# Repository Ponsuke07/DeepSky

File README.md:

View this project on [CADLAB.io](https://cadlab.io/project/1893). 

# DeepSky
*DeepSky* is a Open Source JTAG Adapter based on FTDI FT2232.  
*Deepsky* is also designed JTAGKey clone.

# Supported Software
[OpenOCD][1] support ([config file](./conf/openocd/deepsky.cfg)).  

[1]:http://openocd.org/

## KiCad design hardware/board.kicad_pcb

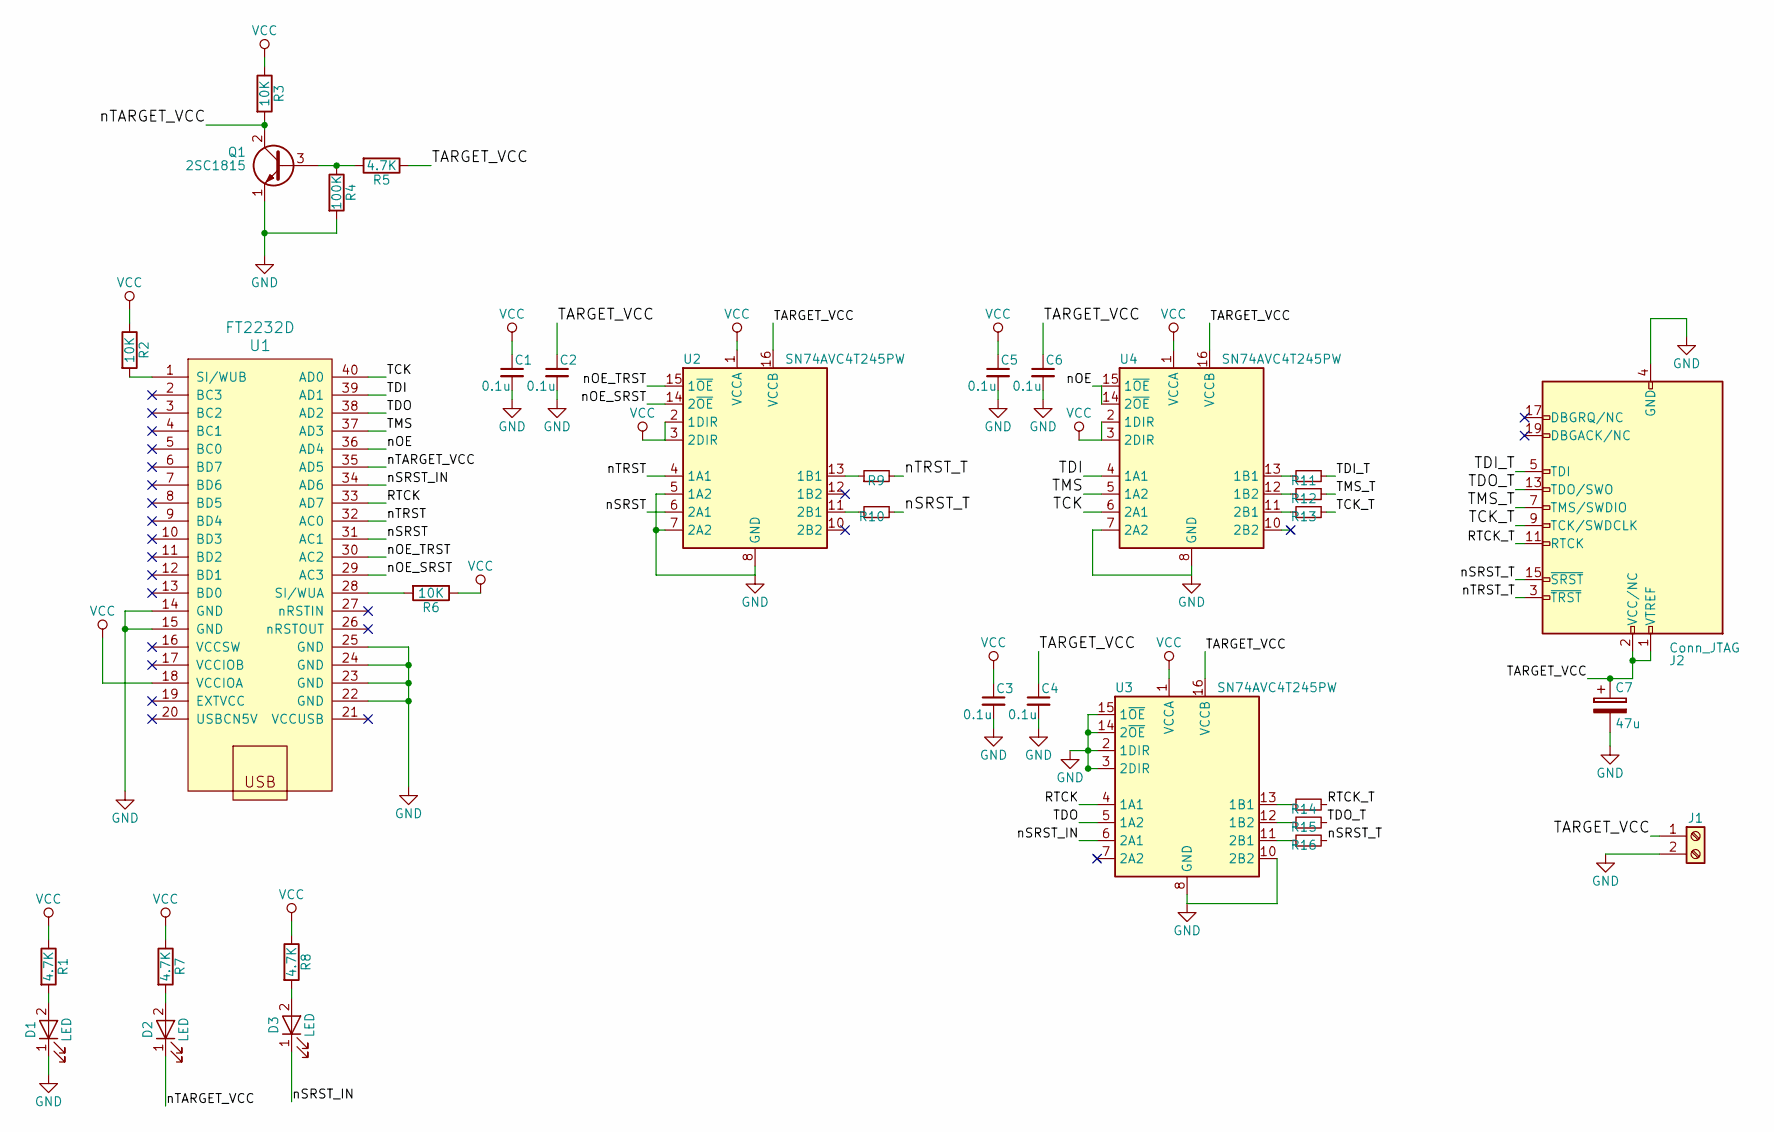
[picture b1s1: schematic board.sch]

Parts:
C1, C2, C3, C4, C5, C6: 0.1u; C_0805_HandSoldering
C7: 47u; CP_Elec_8x6.7
D1, D2, D3: LED; LED_D3.0mm
J1: Screw_Terminal_01x02; TerminalBlock_Phoenix_MKDS1.5-2pol
J2: Conn_JTAG; Pin_Header_Straight_2x10_Pitch2.54mm
Q1: 2SC1815; TO-92_Inline_Wide
R1, R5, R7, R8: 4.7K; R_0805_HandSoldering
R2, R3, R6: 10K; R_0805_HandSoldering
R4: 100K; R_Axial_DIN0207_L6.3mm_D2.5mm_P10.16mm_Horizontal
R9, R10, R11, R12, R13, R14, R15, R16: 68; R_0805_HandSoldering
U1: FT2232D; AE-FT2232
U2, U3, U4: SN74AVC4T245PW; TSSOP-16_4.4x5mm_P0.65mm

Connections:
/RTCK: U1.33 (AD7), U3.4 (1A1)
/RTCK_T: J2.11 (RTCK), R14.2
/TARGET_VCC: C2.1, C4.1, C6.1, C7.1, J1.1, J2.1 (VTREF), J2.2 (VCC/NC), R5.1, U2.16 (VCCB), U3.16 (VCCB), U4.16 (VCCB)
/TCK: U1.40 (AD0), U4.6 (2A1)
/TCK_T: J2.9 (TCK/SWDCLK), R13.2
/TDI: U1.39 (AD1), U4.4 (1A1)
/TDI_T: J2.5 (TDI), R11.2
/TDO: U1.38 (AD2), U3.5 (1A2)
/TDO_T: J2.13 (TDO/SWO), R15.2
/TMS: U1.37 (AD3), U4.5 (1A2)
/TMS_T: J2.7 (TMS/SWDIO), R12.2
/nOE: U1.36 (AD4), U4.14 (2~OE), U4.15 (1~OE)
/nOE_SRST: U1.29 (AC3), U2.14 (2~OE)
/nOE_TRST: U1.30 (AC2), U2.15 (1~OE)
/nSRST: U1.31 (AC1), U2.6 (2A1)
/nSRST_IN: D3.1 (K), U1.34 (AD6), U3.6 (2A1); also elsewhere on the board
/nSRST_T: J2.15 (~SRST~), R10.2, R16.2
/nTARGET_VCC: D2.1 (K), Q1.2 (C), R3.2, U1.35 (AD5); also elsewhere on the board
/nTRST: U1.32 (AC0), U2.4 (1A1)
/nTRST_T: J2.3 (~TRST~), R9.2
GND: C1.2, C2.2, C3.2, C4.2, C5.2, C6.2, C7.2, D1.1 (K), J1.2, J2.4 (GND), J2.6 (GND), J2.8 (GND), J2.10 (GND), J2.12 (GND), J2.14 (GND), J2.16 (GND), J2.18 (GND), J2.20 (GND), Q1.1 (E), R4.2, U1.14 (GND), U1.15 (GND), U1.22 (GND), U1.23 (GND), U1.24 (GND), U1.25 (GND), U2.5 (1A2), U2.7 (2A2), U2.8 (GND), U2.9 (GND), U3.2 (1DIR), U3.3 (2DIR), U3.8 (GND), U3.9 (GND), U3.10 (2B2), U3.14 (2~OE), U3.15 (1~OE), U4.7 (2A2), U4.8 (GND), U4.9 (GND); also elsewhere on the board
unnamed 21: D1.2 (A), R1.2; also elsewhere on the board
unnamed 22: D2.2 (A), R7.2; also elsewhere on the board
unnamed 23: D3.2 (A), R8.2; also elsewhere on the board
unnamed: Q1.3 (B), R4.1, R5.2
unnamed: R2.2, U1.1 (SI/WUB)
unnamed: R6.2, U1.28 (SI/WUA)
unnamed: R9.1, U2.13 (1B1)
unnamed: R10.1, U2.11 (2B1)
unnamed: R11.1, U4.13 (1B1)
unnamed: R12.1, U4.12 (1B2)
unnamed: R13.1, U4.11 (2B1)
unnamed: R14.1, U3.13 (1B1)
unnamed: R15.1, U3.12 (1B2)
unnamed: R16.1, U3.11 (2B1)
VCC: C1.1, C3.1, C5.1, R1.1, R2.1, R3.1, R6.1, R7.1, R8.1, U1.18 (VCCIOA), U2.1 (VCCA), U2.2 (1DIR), U2.3 (2DIR), U3.1 (VCCA), U4.1 (VCCA), U4.2 (1DIR), U4.3 (2DIR)

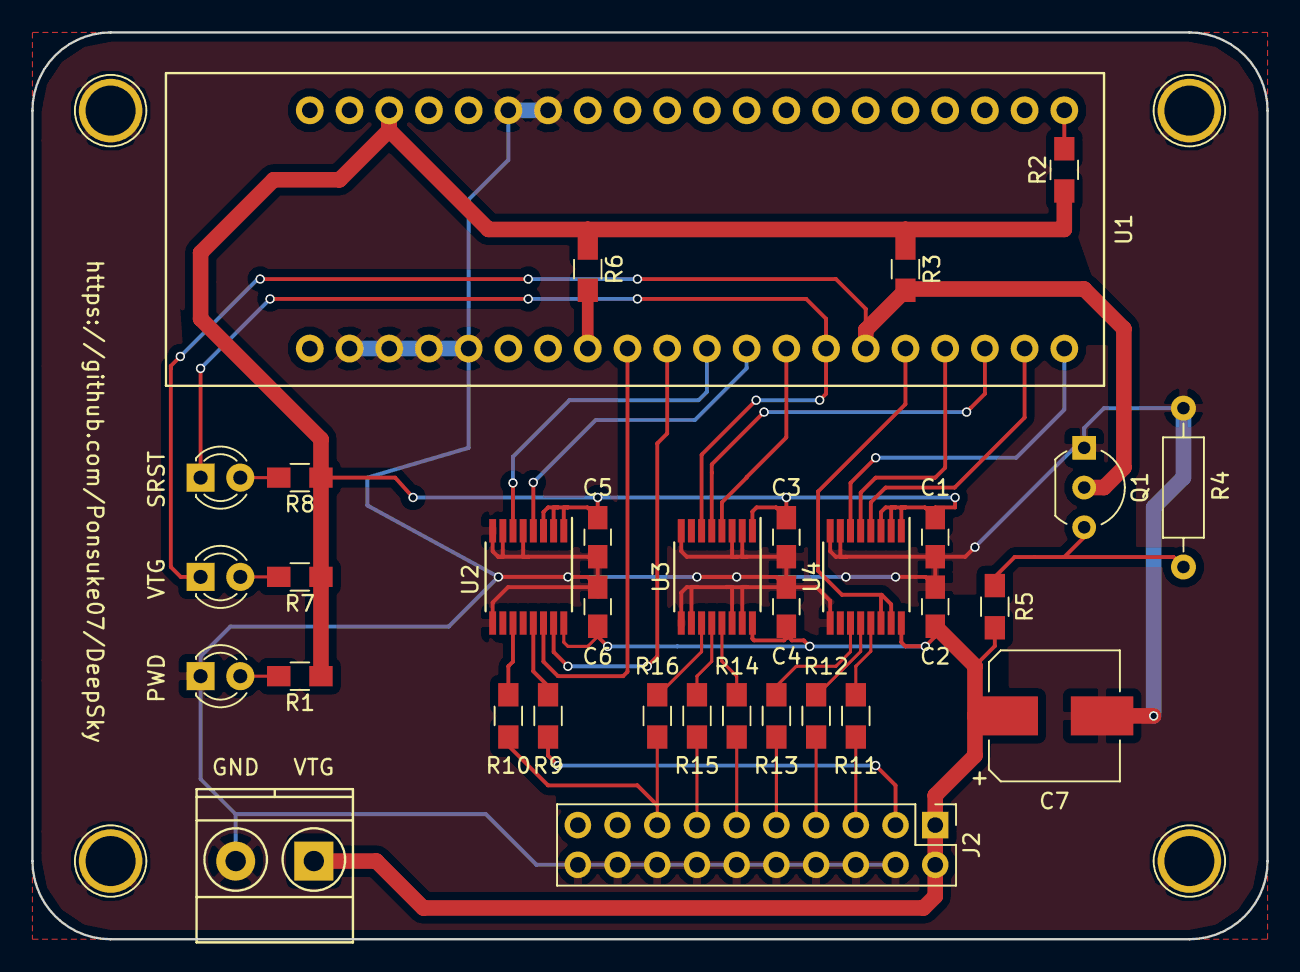
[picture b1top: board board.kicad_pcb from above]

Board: 2 copper layers, 79.0 x 58.0 mm, 33 parts (0 on the bottom side), 36 nets.

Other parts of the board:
PWD: LED; LED_D3.0mm
SRST: LED; LED_D3.0mm
VTG: LED; LED_D3.0mm

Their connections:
/nSRST_IN: SRST.1; also elsewhere on the board
/nTARGET_VCC: VTG.1; also elsewhere on the board
GND: PWD.1; also elsewhere on the board
unnamed 21: PWD.2; also elsewhere on the board
unnamed 22: VTG.2; also elsewhere on the board
unnamed 23: SRST.2; also elsewhere on the board

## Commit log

2019-06-21 Add gitignore for kicad
2019-06-21 Add directory for datasheet
    All files in this directory w/o dat files are ignored by git.
2019-06-22 hardware: Add LEDs and register to protect undershoot
2019-06-22 hardware: Add schematic
2019-06-22 hardware: libs: Add FT2232D USB to Serial convert module
    This module is provided from AKIZUKI DENSHI TSUSHO CO.,LTD.
    Look the below to get more information about it.
    * http://akizukidenshi.com/catalog/g/gM-02990/
2019-06-22 Backlink to CADLAB.io has been added.
2019-06-23 hardware: Bump up the version to 0.1
2019-08-28 hardware: Fix connection of LED
2019-08-28 conf: Add deepsky.cfg for openocd
2019-08-30 hardware: schematic: Extract FT2232 to ft2232.sch
2020-01-12 README: Update
2021-02-21 case: Add simple small case
2021-02-21 conf: Define default adapter_khz
    Set adapter clock to 15MHz by default.
2021-02-21 hardware: Minor update v1.0.1
2021-02-21 case: Update case for pcb v1.0.1
2021-02-21 [WIP] hardware: Add FT2232D
    It will replace AE_FT2232D in the near future.
2021-02-21 hardware: Add bom.ini
